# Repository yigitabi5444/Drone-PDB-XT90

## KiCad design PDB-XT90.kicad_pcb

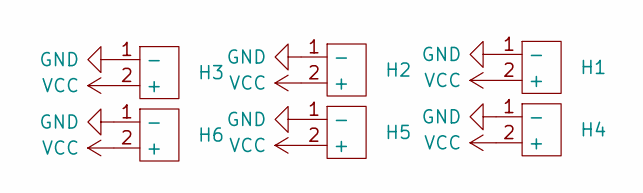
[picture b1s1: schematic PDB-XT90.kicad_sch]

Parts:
H1, H2, H3, H4, H5, H6: XT90; XT90_V

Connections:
GND: H1.1 (-), H2.1 (-), H3.1 (-), H4.1 (-), H5.1 (-), H6.1 (-)
VCC: H1.2 (+), H2.2 (+), H3.2 (+), H4.2 (+), H5.2 (+), H6.2 (+)

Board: 2 copper layers, 6 parts (0 on the bottom side), 2 nets, no tracks yet.

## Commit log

2023-02-16 New PCB
2023-02-16 Added logos
